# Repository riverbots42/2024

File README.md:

Astoria Senior Highschool's robotic's team's code for participating in the 2024 FIRST Robotics Competition

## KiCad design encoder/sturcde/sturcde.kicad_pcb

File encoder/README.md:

# The Stupid Ridiculously-Cheap Drive Encoder

(aka "StuRCDE," pronounced "Sturk-Dee")

## Introduction

A drive encoder is a device that "clicks" whenever a motor or wheel turns, to give the controller an idea where the robot is either in e.g. the rotation of an arm or similar or where the bot is on the field (so we can do autonomous driving).

The big problems with industrial encoders such as the
[US Digital E4T](https://www.andymark.com/products/e4t-oem-miniature-optical-encoder-kit) are that:

1. They're expensive ($40-60 each, and you need at least two of them to track your playfield position).
2. They're not reusable (once attached to a gearbox, removing them effectively destroys them).
3. They're supply-constrained (ordering new ones takes FOREVER through typical channels).

The StuRCDE gets rid of this problem by:

1. Being stupid-simple (and therefore cheap).  Its design consists of two resistors and a rotary car stereo-style encoder switch.
2. Being stupid-simple (and therefore disposable).  Being $100 cheaper than the industrial solutions, who cares if we can't reuse them?
3. Being stupid-simple (and therefore easy-to-source).  So we can order all parts from Amazon or any other online vendor, not just e.g. AndyMark.

## Contents

sturcde/ - The printed circuit board version of this project, using pin headers to connect to the physical wiring.  This is OPTIONAL but makes assembly nicer if one is willing to source boards from a PCB fab like [PCBWay](https://pcbway.com).
sturcde-overview.png - An overview of the whole works and its theory of operation from a top level.
sturcde-wiring.png - How to make one of these without the PCB; just a bit of wire and some solder along with the three components.

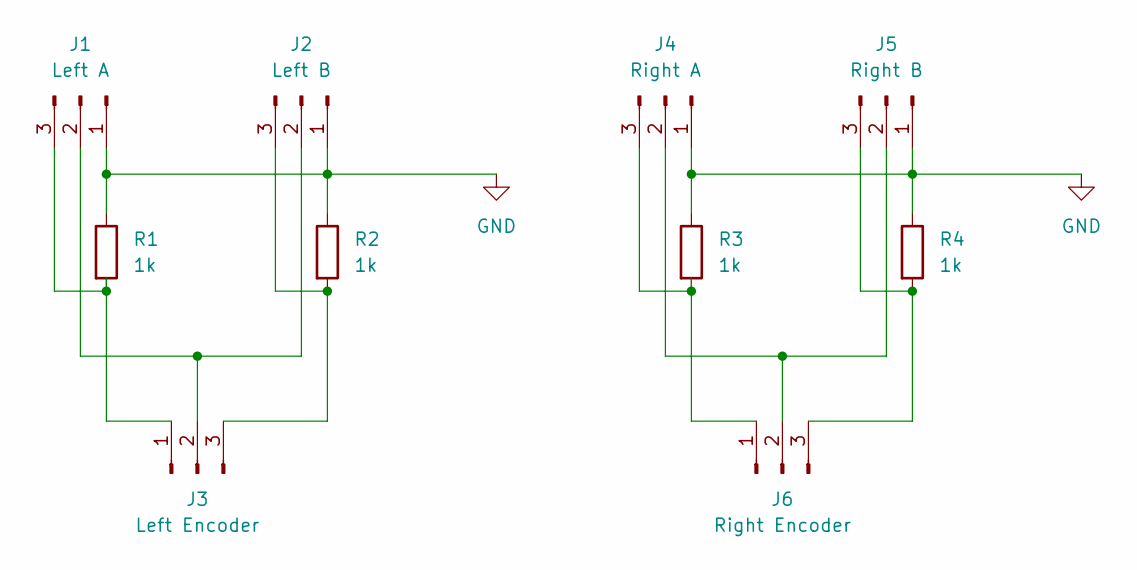
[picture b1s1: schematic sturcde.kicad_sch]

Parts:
J1: Left A; PinHeader_1x03_P2.54mm_Horizontal
J2: Left B; PinHeader_1x03_P2.54mm_Horizontal
J3: Left Encoder; PinHeader_1x03_P2.54mm_Horizontal
J4: Right A; PinHeader_1x03_P2.54mm_Horizontal
J5: Right B; PinHeader_1x03_P2.54mm_Horizontal
J6: Right Encoder; PinHeader_1x03_P2.54mm_Horizontal
R1, R2, R3, R4: 1k; R_Axial_DIN0207_L6.3mm_D2.5mm_P7.62mm_Horizontal

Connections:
GND: J1.1, J2.1, J4.1, J5.1, R1.1, R2.1, R3.1, R4.1
unnamed: J1.2, J2.2, J3.2
unnamed: J1.3, J3.1, R1.2
unnamed: J2.3, J3.3, R2.2
unnamed: J4.2, J5.2, J6.2
unnamed: J4.3, J6.1, R3.2
unnamed: J5.3, J6.3, R4.2

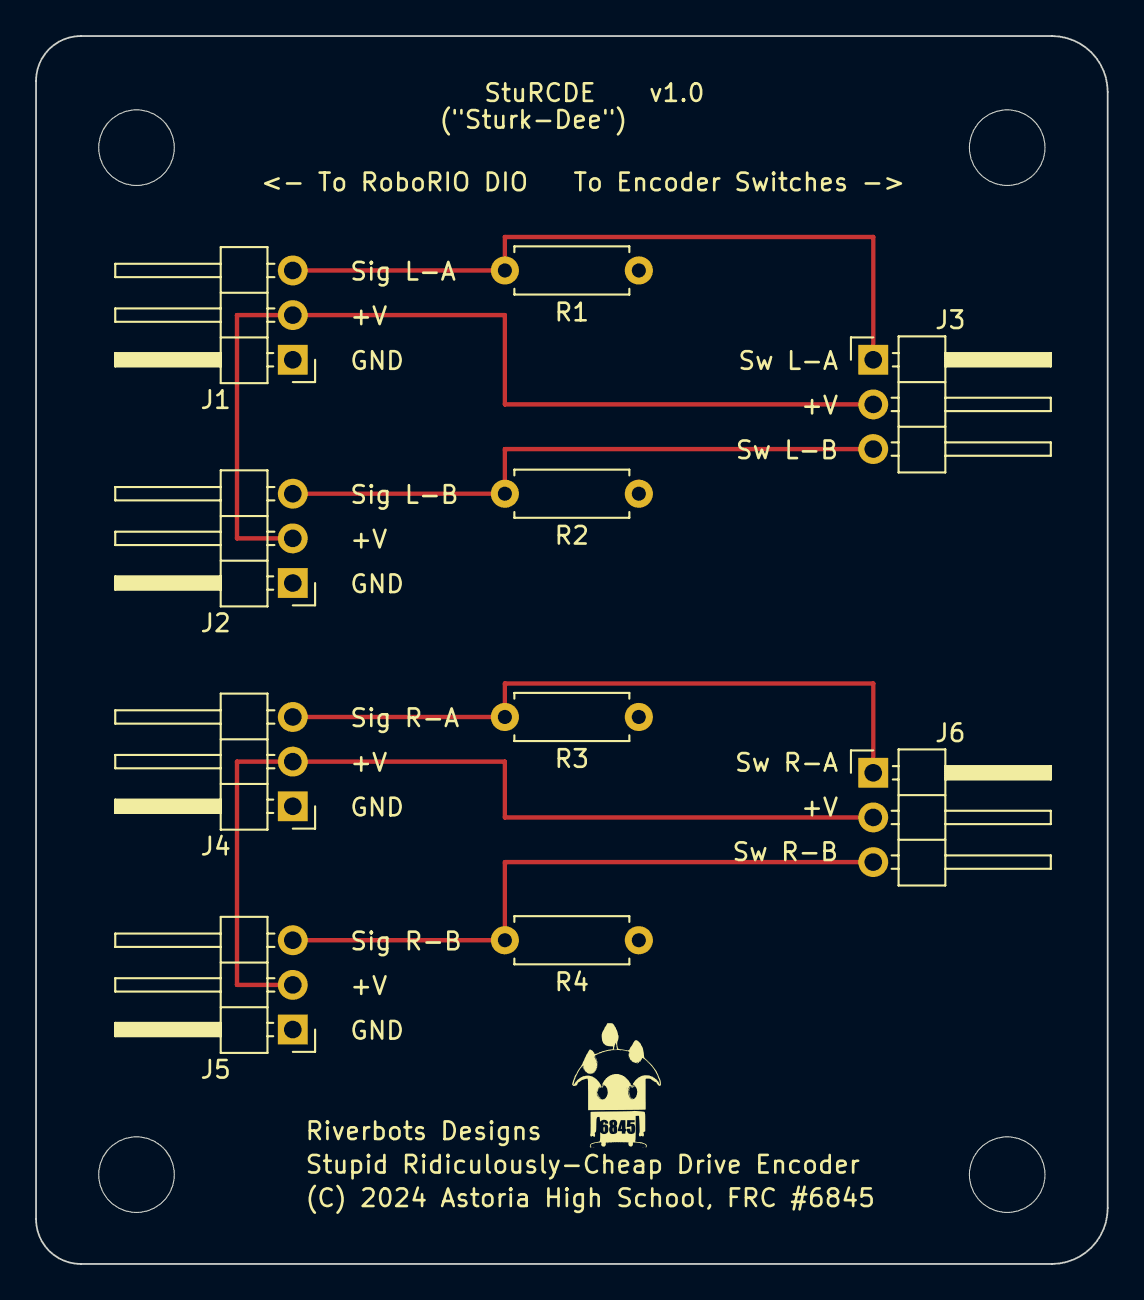
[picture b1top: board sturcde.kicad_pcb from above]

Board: 2 copper layers, 61.0 x 69.8 mm, 10 parts (0 on the bottom side), 7 nets.

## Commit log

2023-11-13 First draft of doorbell for testing.
2023-11-14 Min ver to JDK 8
2023-11-16 Refactor to move play() to a func.
2023-11-16 Add Java Servlet engine (embedded Jetty).
2023-11-16 Move around files so we can embed the MP3 inside the JAR with the program; add Status Servlet, connect up everything else.
2023-11-16 Add comments.
2023-11-29 New Robot Code
2023-11-30 Change port number, add Ansible playbooks.
2024-01-06 Aidan Unfinished
2024-01-06 Aidan Unfinished Drive
2024-01-09 New Code Preset for 2024 Lib
2024-01-10 working
2024-01-10 Cleaned Files
2024-01-11 Added 4 motor Differential Drive.
2024-01-11 Added 4 Motor Differential Drive
2024-01-11 Added PhotonVision + unnamed camera
2024-01-18 Spark 1 Works!!
2024-01-19 Ultrasonic Groundwork
2024-01-20 Discovered Ultrasonic Problem
2024-01-23 Baby Bot Arcade Drive
2024-01-25 Added Cad files
2024-01-25 Moved some files and removed everything not CAD
2024-01-25 Auto & Simulation Framework
2024-01-25 Create NoteGamePiece.dwg
    A Note The Game piece for the 2024 First Robotics competition crescendo
2024-01-25 Sim probably shouldn't get uploaded; I didn't realize it only changed to this while running
2024-01-26 Added a reference photo of the incomplete drivebase and part layouts with dimensions
2024-01-28 Code Hell
2024-02-01 Spark Max Code Working!!
2024-02-01 Cleaned a bit and forgot to commit
2024-02-01 Cleaned last night and want to upload before further work
2024-02-01 Added Photovision things (imports, methods, vars). Needs test.
2024-02-02 Framework For LEDs
2024-02-02 add png to integer conversion program
2024-02-02 Added CAN Spark Max Functionality
2024-02-02 Deleted accidental class
2024-02-03 Added Motor Contoller Group basically.
2024-02-03 Working Motors. Quite fast though.
2024-02-03 LED debugging (I want to pull main)
2024-02-04 Add png file filtering and subdirectory scanning.
2024-02-04 Working LED Snake
2024-02-04 Add algorithm for translating x,y to index.
2024-02-04 Add encoder docs.
2024-02-06 LED suggestions from BJ (can't run yet)
2024-02-07 added algorithm. Strobes and overruns 20 ms loop (loop gets slower and bugs out)
2024-02-07 VictorSPX added
2024-02-07 Small LED Addition and Preperation
2024-02-09 added animation and frame classes
2024-02-09 add intitial graphics
2024-02-09 Untested LED added and VictorSPX import broke
2024-02-10 Cleared out old comments
2024-02-10 Aidan fixed com import
2024-02-10 Add comments, cleanup debug code a bit, and clean up formatting.
2024-02-10 More format cleanup.
2024-02-10 Tiny LED change I can't test yet
2024-02-10 Basic Encoder
2024-02-10 Add rest of source generator for Animations.java and friends; add test.
2024-02-10 fix makefile
2024-02-11 Not Working!!
2024-02-13 Encoder Code Works
2024-02-13 LED commented out to run teleop
2024-02-13 Winch code modified but not working
2024-02-14 Removed Non LED Essentials
2024-02-14 Inverted Wheels
2024-02-14 Add StuRCDE PCB and README.
2024-02-14 Add logo; general cleanups and prep for pcbway.
2024-02-14 Added Parabolic Drive
2024-02-17 Added Pnuematics. Still haven't tested PhotonVision through Co-Processor
2024-02-17 Swap rows/cols so things show up in the expected order.
2024-02-17 LEDs work!!
2024-02-17 Animation set up
2024-02-17 Parabolic Drive Works
2024-02-17 Rename Animations to AnimationList.
2024-02-18 Stupid solution to work around method size limits in Java.
2024-02-18 Working Winch Control
2024-02-18 Add exceptions.
2024-02-24 Connects to PhotonVision Co-Processor. Sends target info.
2024-02-24 Added Distance and Rotation calculations to autoPeriodic. Needs testing and actual measurements.
2024-02-25 Add animated GIFs.
2024-02-25 Pathing Based on Field Position
2024-02-25 Modify gif2pnglist to properly marginate 32x16 GIFs, add notes graphics.
2024-02-26 Working Position Selection
2024-02-26 Added a lot of changes. Added FrameList.
2024-02-28 BJ LED Code
2024-03-03 Added many things. Got to go sorry!
2024-03-05 Added some comments!
2024-03-05 Make shifty-eyes last longer.
2024-03-06 Added Brushed instead Of Brushless
2024-03-06 Added things
2024-03-06 Workingish Auto
2024-03-07 Essentially merged the Aidaens branches
2024-03-07 Victors To TalonSRXs
2024-03-07 Aidan Review
2024-03-07 Add sponsors crawl.
2024-03-07 Changed FireButton to Driver Preference
2024-03-07 Reduce Drive Speed
2024-03-13 PathPlanner Preperation
2024-03-13 PathPlannerPrep
2024-03-13 Aidan's Changes
2024-03-14 Working On Adding Auto Command System
2024-03-15 Deleted PathPlanner System We're Going to Localize With AprilTags One Button Fire System
2024-03-15 Work
2024-03-15 It's not uploading
2024-03-19 Rev then shoot not working. Need to fix tick/timer stuff.
2024-03-19 Firing Works
2024-03-19 Remove PathPlanner and Fix Firing
2024-03-19 Unfinished code
2024-03-19 Deleted Bad Files
2024-03-19 Added Parabolic Method back
2024-03-19 Not Tested yet!
2024-03-20 Small changes
2024-03-20 LEDs Work
2024-03-20 Fixed Drive?
2024-03-20 Fixed Fire Sequence
2024-03-20 Cleaned Code
2024-03-20 Add max 2.5A request for powah.
2024-03-20 Fix logic for calculation of max_current.
2024-03-21 Fixed Individual Intake
2024-03-21 Added Turbo And Limit Launch Speed
2024-10-08 Add sturcde backup.

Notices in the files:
encoder/sturcde/sturcde.kicad_pcb:
(C) 2024 Astoria High School, FRC #6845
